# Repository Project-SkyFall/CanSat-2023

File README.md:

# Disclaimer
This README isn't finished and will be edited in near future

# CanSat-2023
This is a repository of the Czech CanSat team Project SkyFall, winner of CanSat's 2023 Czech national round

<div align="center">
  
</div>

## Documentation

<!-- About team -->

## About the team

  ### Vít Brázda
  <table><tr>
    <td width="250"></td>
    <td>Vít is responsible for data visualization running on ground station, as well as making index of habitability of planet, where CanSat is landing. He has a lot of experience regarding Python.</td>
  </tr></table>

  ### David Haisman
  <table><tr>
    <td width="250"></td>
    <td>David handles electronics and programming on our CanSat. He designed PCB's, made some libraries and wrote the whole CanSat code. During the development of the CanSat he gained a lot of experience regarding PCB design and programming in C++.</td>
  </tr></table>

  ### Radim Leština
  <table><tr>
    <td width="250"></td>
    <td>Radim is in charge of designing the outer construction of the CanSat itself. He has a lot of experience in designing and 3D printing mechanical contraptions.</td>
  </tr></table>

  ### Václav Horáček
  <table><tr>
    <td width="250"></td>
    <td>Václav is in charge of multiple departments, mainly the ones for documentation and recovery. In documentation he made the styles, graphics and oversees the documentation making process. His contribution in the recovery department is designing and sewing the CanSat's parachute.</td>
  </tr></table>

  ### Lukáš Nastoupil
  <table><tr>
    <td width="250"></td>
    <td>Lukáš designed and made the ground station, which is an essential part for our secondary mission. He designed the PCB's, modeled and programmed the ground station. He also worked on the real-time transmission of video from CanSat down to the ground station.</td>
  </tr></table>

  ### Adam Keřka
  <table><tr>
    <td width="250"></td>
    <td>Adam leads the team itself and also the department of publicity. This mainly includes maintaining social networks accounts and communicating with sponsors. He also designed a lot of the graphics used in advertising and posts on social networks.</td>
  </tr></table>

  ### Vladimír Kašpar
  Ing. Vladimír Kašpar is our mentor in the CanSat competition. We chose Vladimír Kašpar as our mentor based on his experience. In the CanSat 2019 he was a mentor of team Charles the fourth that made it to the European finale. He is also an electronics teacher at SPŠE a VOŠ Pardubice.

  ### Jan Novotný
  Jan Novotný is a freelance developer who makes web and mobile applications. He programmed the Project SkyFall webpage and supports our team on various other competitions and outgoings.

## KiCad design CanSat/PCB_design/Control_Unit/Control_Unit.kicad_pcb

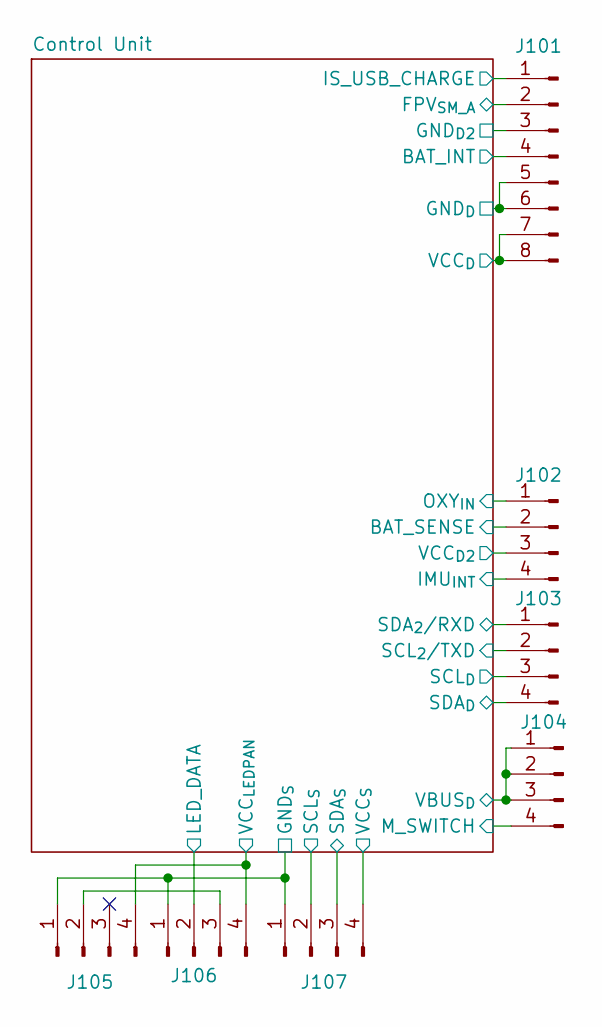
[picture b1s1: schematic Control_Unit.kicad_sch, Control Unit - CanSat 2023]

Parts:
J101: Conn_02x04_Male; PinHeader_2x04_P2.54mm_Vertical
J102, J103, J104: Conn_02x02_Male; PinHeader_2x02_P2.54mm_Vertical
J105, J106, J107: 009155004541006

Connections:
/Control Unit/BATT_INT: J101.4; also elsewhere on the board
/Control Unit/BAT_SENSE: J102.2; also elsewhere on the board
/Control Unit/FPV_{SM_A}: J101.2; also elsewhere on the board
/Control Unit/GND: J101.3, J101.5, J101.6, J105.1, J106.1, J107.1; also elsewhere on the board
/Control Unit/IMU_{INT}: J102.4; also elsewhere on the board
/Control Unit/IS_USB_CHARGE: J101.1; also elsewhere on the board
/Control Unit/LED_DATA: J106.2; also elsewhere on the board
/Control Unit/M_SWITCH: J104.4; also elsewhere on the board
/Control Unit/OXY_{IN}: J102.1; also elsewhere on the board
/Control Unit/SCL: J103.3, J107.2; also elsewhere on the board
/Control Unit/SCL_{2}/TXD: J103.2; also elsewhere on the board
/Control Unit/SDA: J103.4, J107.3; also elsewhere on the board
/Control Unit/SDA_{2}/RXD: J103.1; also elsewhere on the board
/Control Unit/VBUS: J104.1, J104.2, J104.3; also elsewhere on the board
/Control Unit/VCC: J101.7, J101.8, J102.3, J107.4; also elsewhere on the board
/Control Unit/VCC_{LEDPAN}: J105.4, J106.4; also elsewhere on the board
unnamed: J105.2, J106.3

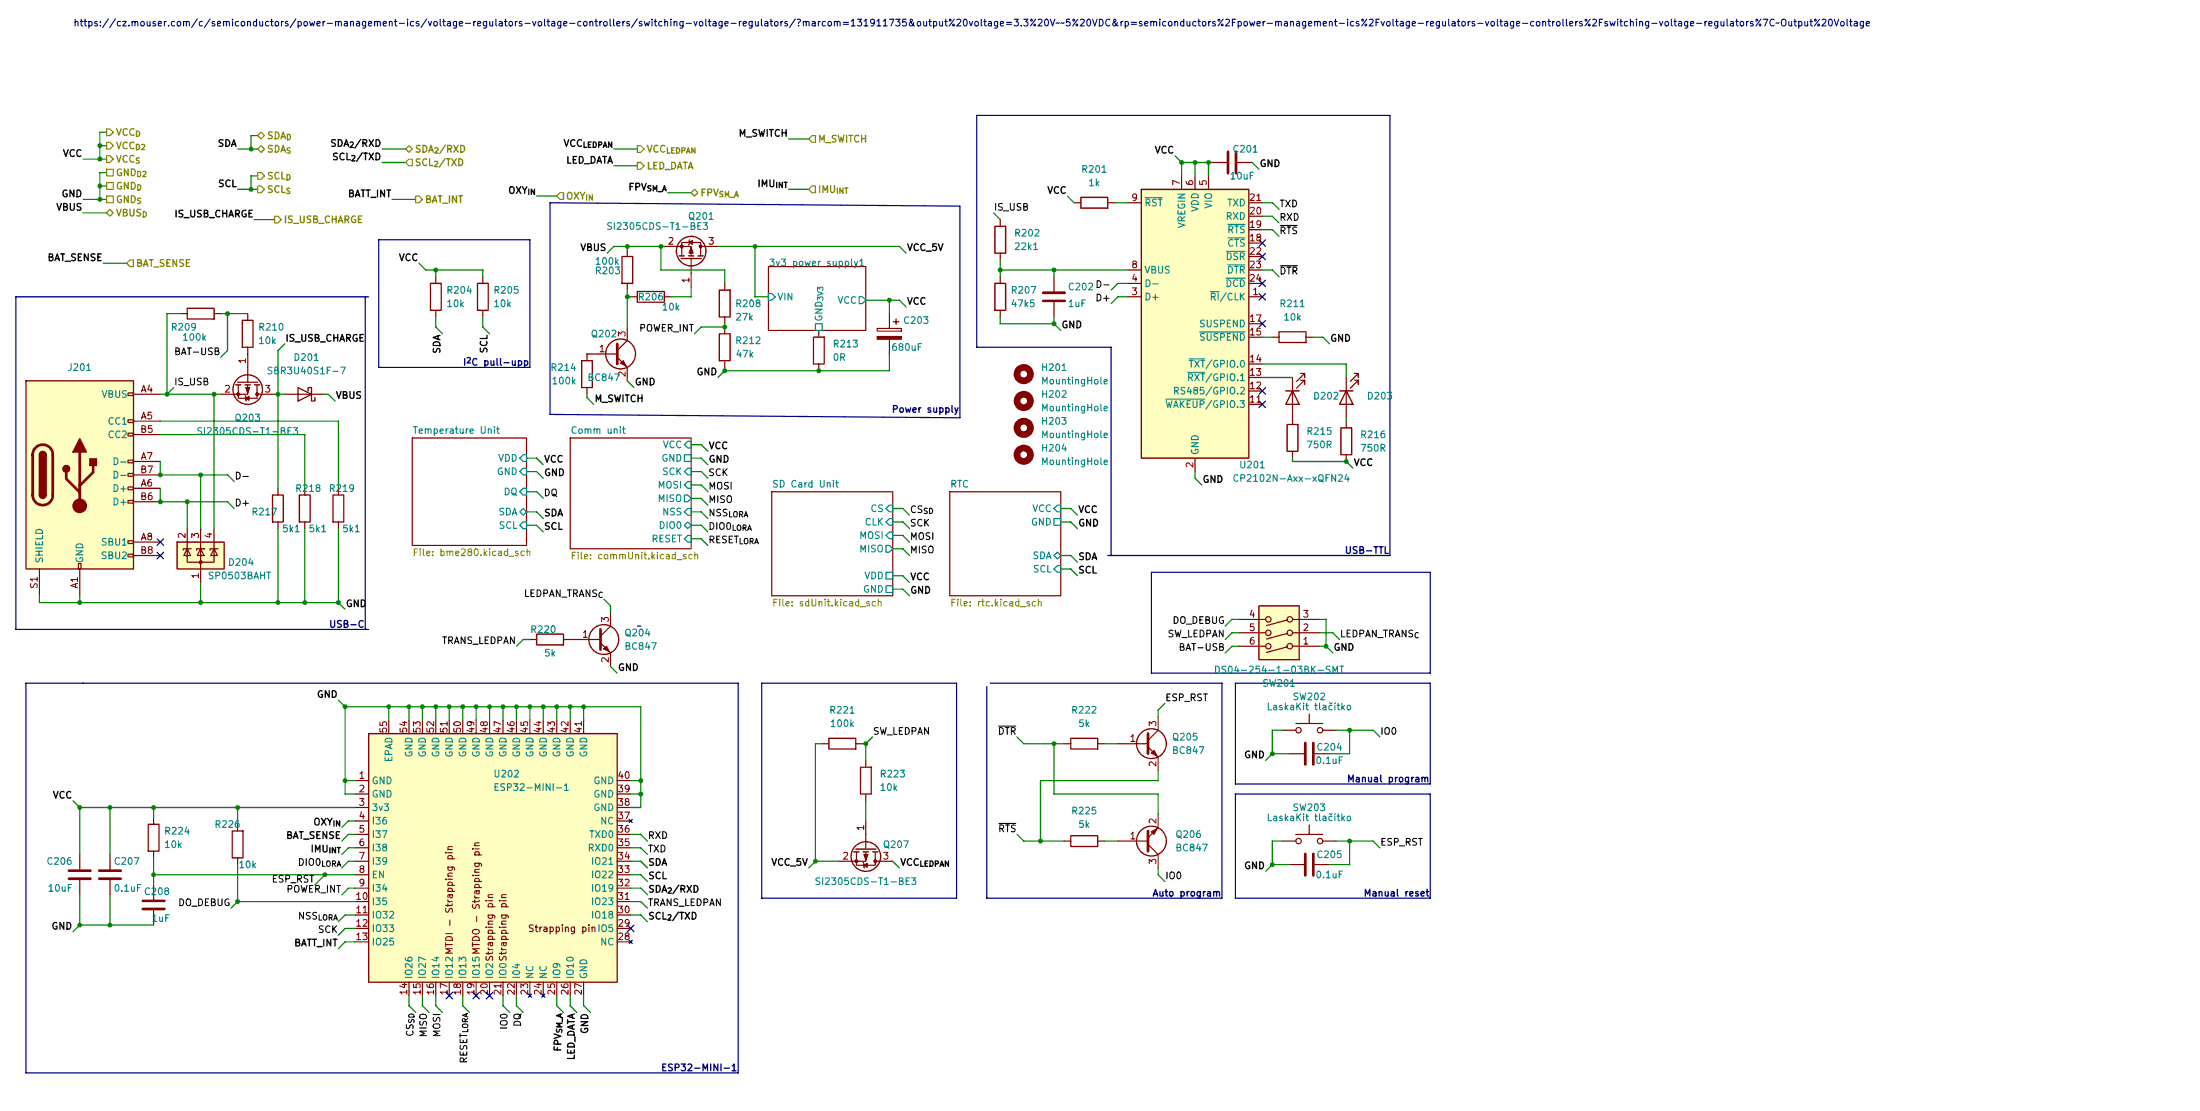
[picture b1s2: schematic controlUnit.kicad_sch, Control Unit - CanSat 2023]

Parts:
C201, C206: 10uF; C_0805_2012Metric
C202, C208: 1uF; C_0805_2012Metric
C203: 680uF; CP_Elec_6.3x7.7
C204, C205, C207: 0.1uF; C_0805_2012Metric
D201: SBR3U40S1F-7; D_SOD-123F
D202, D203: APT2012LSECK/J4-PRV; LED_0805_2012Metric
D204: SP0503BAHT; SOT-143
H201, H202, H203, H204: MountingHole; MountingHole_3.2mm_M3
J201: USB4110-GF-A; USB4110GFA
Q201, Q203, Q207: SI2305CDS-T1-BE3; SOT-23
Q202, Q204, Q205, Q206: BC847; SOT-23
R201: 1k; R_0805_2012Metric
R202: 22k1; R_0805_2012Metric
R203, R209, R214, R221: 100k; R_0805_2012Metric
R204, R205, R206, R210, R211, R223, R224, R226: 10k; R_0805_2012Metric
R207: 47k5; R_0805_2012Metric
R208: 27k; R_0805_2012Metric
R212: 47k; R_0805_2012Metric
R213: 0R; R_1206_3216Metric
R215, R216: 750R; R_0805_2012Metric
R217, R218, R219: 5k1; R_0805_2012Metric
R220, R222, R225: 5k; R_0805_2012Metric
SW201: DS04-254-1-03BK-SMT; SW_DIP_SPSTx03_Slide_Omron_A6S-310x_W8.9mm_P2.54mm
SW202, SW203: LaskaKit tlačítko; Tlačítko SMD LaskaKit
U201: CP2102N-Axx-xQFN24; QFN-24-1EP_4x4mm_P0.5mm_EP2.6x2.6mm
U202: ESP32-MINI-1

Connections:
/Control Unit/3v3 power supply1/GND_{3V3}: R213.2; also elsewhere on the board
/Control Unit/BAT-USB: R209.2, R210.1, SW201.6
/Control Unit/BATT_INT: U202.13 (IO25); also elsewhere on the board
/Control Unit/BAT_SENSE: U202.5 (I37); also elsewhere on the board
/Control Unit/CS_{SD}: U202.14 (IO26); also elsewhere on the board
/Control Unit/D+: D204.2 (K), J201.A6 (D+), J201.B6 (D+), U201.3 (D+)
/Control Unit/D-: D204.3 (K), J201.A7 (D-), J201.B7 (D-), U201.4 (D-)
/Control Unit/DIO0_{LORA}: U202.7 (I39); also elsewhere on the board
/Control Unit/DO_DEBUG: R226.1, SW201.4, U202.10 (I35)
/Control Unit/DQ: U202.22 (I04); also elsewhere on the board
/Control Unit/ESP_RST: C205.2, C208.1, Q205.3 (C), R224.2, SW203.2, U202.8 (EN)
/Control Unit/FPV_{SM_A}: U202.25 (IO9); also elsewhere on the board
/Control Unit/GND: C201.2, C202.2, C203.2, C204.1, C205.1, C206.2, C207.2, C208.2, D204.1 (A), J201.A1 (GND), J201.A12 (GND), J201.B1 (GND), J201.B12 (GND), J201.S1 (SHIELD), Q202.2 (E), Q204.2 (E), R207.2, R211.2, R212.2, R213.1, R217.2, R218.2, R219.2, SW201.1, SW201.3, SW202.1, SW203.1, U201.2 (GND), U201.25 (GND), U202.1 (GND), U202.2 (GND), U202.27 (GND), U202.38 (GND), U202.39 (GND), U202.40 (GND), U202.41 (GND), U202.42 (GND), U202.43 (GND), U202.44 (GND), U202.45 (GND), U202.46 (GND), U202.47 (GND), U202.48 (GND), U202.49 (GND), U202.50 (GND), U202.51 (GND), U202.52 (GND), U202.53 (GND), U202.54 (GND), U202.55 (EPAD); also elsewhere on the board
/Control Unit/IMU_{INT}: U202.6 (I38); also elsewhere on the board
/Control Unit/IO0: C204.2, Q206.3 (C), SW202.2, U202.21 (IO0)
/Control Unit/IS_USB: D204.4 (K), J201.A4 (VBUS), J201.A9 (VBUS), J201.B4 (VBUS), J201.B9 (VBUS), Q203.2 (S), R202.2, R209.1
/Control Unit/IS_USB_CHARGE: D201.2 (A), Q203.3 (D), R217.1; also elsewhere on the board
/Control Unit/LEDPAN_TRANS_{C}: Q204.3 (C), SW201.2
/Control Unit/LED_DATA: U202.26 (IO10); also elsewhere on the board
/Control Unit/MISO: U202.15 (IO27); also elsewhere on the board
/Control Unit/MOSI: U202.16 (IO14); also elsewhere on the board
/Control Unit/M_SWITCH: R214.1; also elsewhere on the board
/Control Unit/NSS_{LORA}: U202.11 (IO32); also elsewhere on the board
/Control Unit/OXY_{IN}: U202.4 (I36); also elsewhere on the board
/Control Unit/POWER_INT: R208.1, R212.1, U202.9 (I34)
/Control Unit/RESET_{LORA}: U202.18 (IO13); also elsewhere on the board
/Control Unit/RXD: U201.20 (RXD), U202.36 (TXD0)
/Control Unit/SCK: U202.12 (IO33); also elsewhere on the board
/Control Unit/SCL: R205.2, U202.33 (IO22); also elsewhere on the board
/Control Unit/SCL_{2}/TXD: U202.30 (IO18); also elsewhere on the board
/Control Unit/SDA: R204.2, U202.34 (IO21); also elsewhere on the board
/Control Unit/SDA_{2}/RXD: U202.32 (IO19); also elsewhere on the board
/Control Unit/SW_LEDPAN: R221.2, R223.2, SW201.5
/Control Unit/TRANS_LEDPAN: R220.1, U202.31 (IO23)
/Control Unit/TXD: U201.21 (TXD), U202.35 (RXD0)
/Control Unit/VBUS: D201.1 (K), Q201.2 (S), R203.1, R208.2; also elsewhere on the board
/Control Unit/VCC: C201.1, C203.1, C206.1, C207.1, R201.1, R204.1, R205.1, R215.1, R216.1, R224.1, R226.2, U201.5 (VIO), U201.6 (VDD), U201.7 (VREGIN), U202.3 (3v3); also elsewhere on the board
/Control Unit/VCC_5V: Q201.3 (D), Q207.2 (S), R221.1; also elsewhere on the board
/Control Unit/VCC_{LEDPAN}: Q207.3 (D); also elsewhere on the board
/Control Unit/~DTR: Q206.2 (E), R222.1, U201.23 (~DTR)
/Control Unit/~RTS: Q205.2 (E), R225.1, U201.19 (~RTS)
unnamed: C202.1, R202.1, R207.1, U201.8 (VBUS)
unnamed: D202.1 (K), U201.13 (~RXT/GPIO.1)
unnamed: D202.2 (A), R215.2
unnamed: D203.1 (K), U201.14 (~TXT/GPIO.0)
unnamed: D203.2 (A), R216.2
unnamed: J201.A5 (CC1), R219.1
unnamed: J201.B5 (CC2), R218.1
unnamed: Q201.1 (G), R206.1
unnamed: Q202.1 (B), R214.2
unnamed: Q202.3 (C), R203.2, R206.2
unnamed: Q203.1 (G), R210.2
unnamed: Q204.1 (B), R220.2
unnamed: Q205.1 (B), R222.2
unnamed: Q206.1 (B), R225.2
unnamed: Q207.1 (G), R223.1
unnamed: R201.2, U201.9 (~RST)
unnamed: R211.1, U201.15 (~SUSPEND)

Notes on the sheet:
USB-TTL
I^{2}C pull-upp
Auto program
ESP32-MINI-1
USB-C
Power supply
Manual reset
https://cz.mouser.com/c/semiconductors/power-management-ics/voltage-regulators-voltage-controllers/switching-voltage-regulators/?marcom=131911735&output%20voltage=3.3%20V~~5%20VDC&rp=semiconductors%2Fpower-management-ics%2Fvoltage-regulators-voltage-controllers%2Fswitching-voltage-regulators%7C~Out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
Manual program

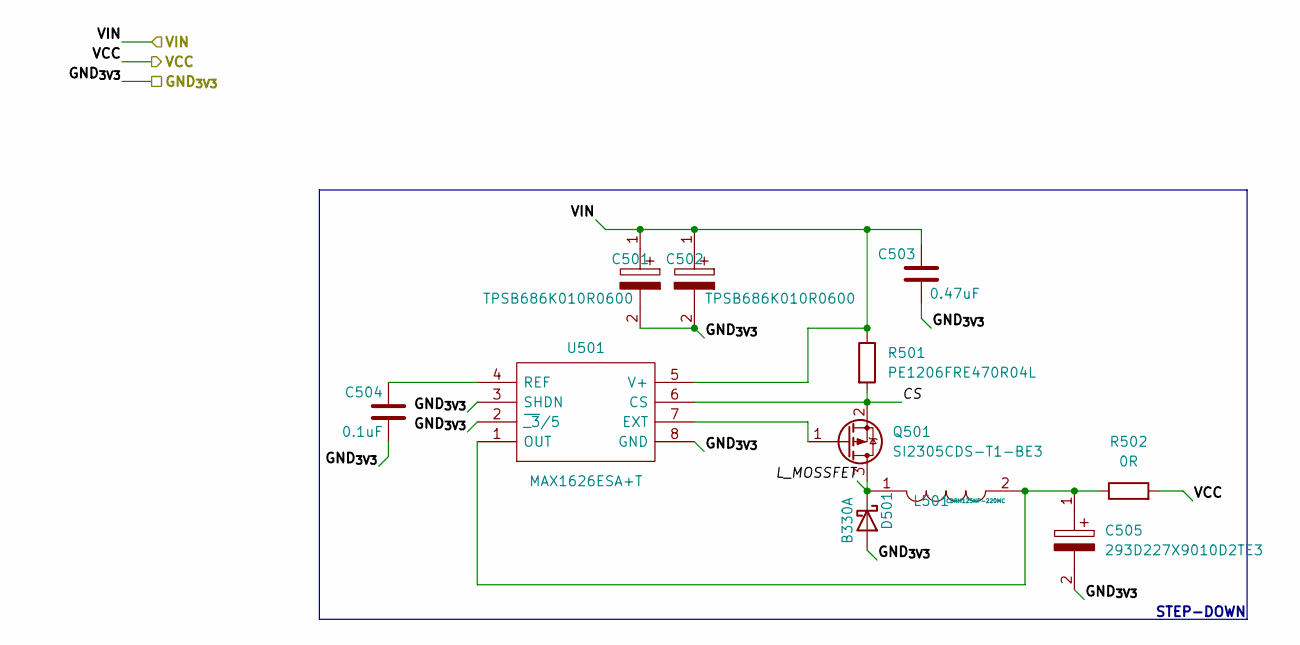
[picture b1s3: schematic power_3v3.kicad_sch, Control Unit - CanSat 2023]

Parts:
C501, C502: TPSB686K010R0600; CP_EIA-3528-21_Kemet-B; Mouser Part Number 581-TPSB686K010R0600
C503: 0.47uF; C_0805_2012Metric
C504: 0.1uF; C_0805_2012Metric
C505: 293D227X9010D2TE3; CP_EIA-7343-31_Kemet-D; Mouser Part Number 74-293D227X9010D2TE3
D501: B330A; D_SMA
L501: CDRH125NP-220MC; CDRH125101MC; Mouser Part Number 851-CDRH125NP-220MC
Q501: SI2305CDS-T1-BE3; SOT-23
R501: PE1206FRE470R04L; R_1206_Current
R502: 0R; R_1206_3216Metric
U501: MAX1626ESA+T; SOIC127P600X175-8N; Mouser Part Number 700-MAX1626ESAT

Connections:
/Control Unit/3v3 power supply1/CS: Q501.2 (S), R501.2, U501.6 (CS)
/Control Unit/3v3 power supply1/GND_{3V3}: C501.2, C502.2, C503.2, C504.2, C505.2, D501.2 (A), U501.2 (~_3/5), U501.3 (SHDN), U501.8 (GND); also elsewhere on the board
/Control Unit/3v3 power supply1/L_MOSSFET: D501.1 (K), L501.1, Q501.3 (D)
/Control Unit/VCC: R502.2; also elsewhere on the board
/Control Unit/VCC_5V: C501.1, C502.1, C503.1, R501.1, U501.5 (V+); also elsewhere on the board
unnamed: C504.1, U501.4 (REF)
unnamed: C505.1, L501.2, R502.1, U501.1 (OUT)
unnamed: Q501.1 (G), U501.7 (EXT)

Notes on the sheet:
STEP-DOWN

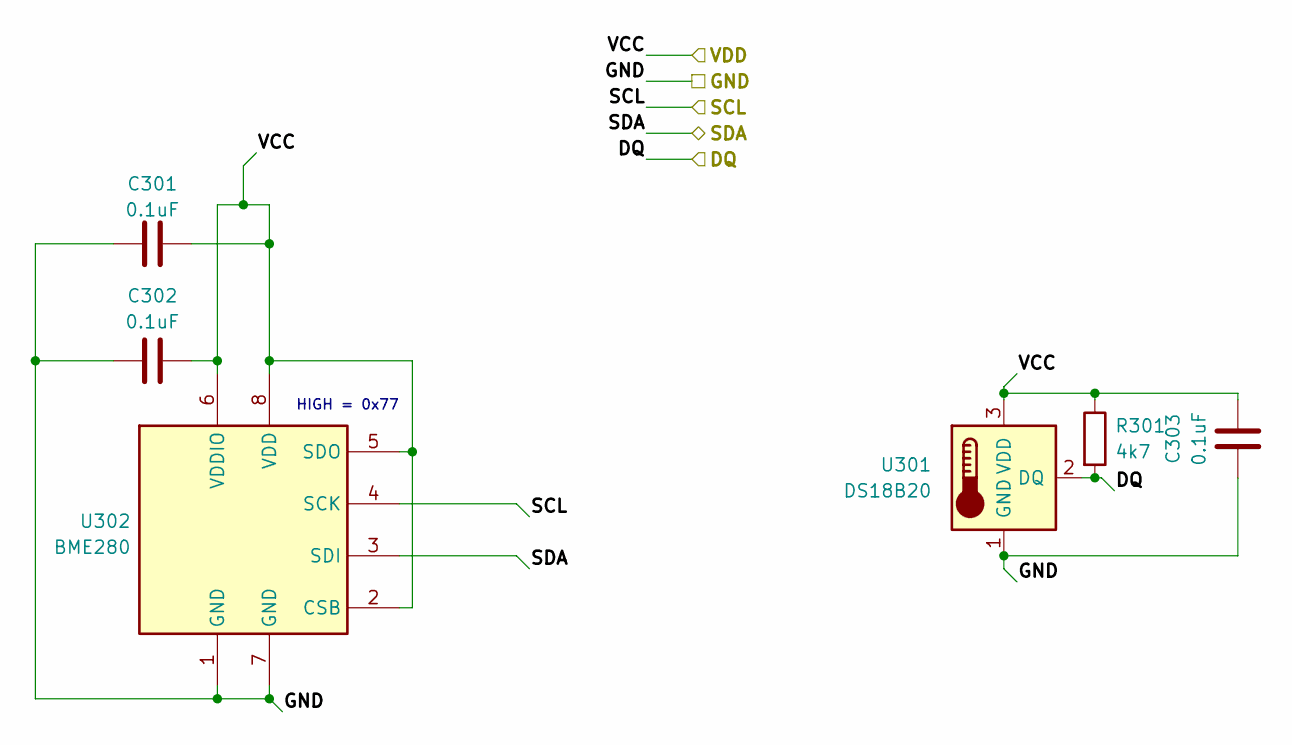
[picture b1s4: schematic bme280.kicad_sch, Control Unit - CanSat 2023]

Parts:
C301, C302, C303: 0.1uF; C_0805_2012Metric
R301: 4k7; R_0805_2012Metric
U301: DS18B20; TO-92_Inline
U302: BME280; Bosch_LGA-8_2.5x2.5mm_P0.65mm_ClockwisePinNumbering

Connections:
/Control Unit/DQ: R301.2, U301.2 (DQ); also elsewhere on the board
/Control Unit/GND: C301.2, C302.2, C303.2, U301.1 (GND), U302.1 (GND), U302.7 (GND); also elsewhere on the board
/Control Unit/SCL: U302.4 (SCK); also elsewhere on the board
/Control Unit/SDA: U302.3 (SDI); also elsewhere on the board
/Control Unit/VCC: C301.1, C302.1, C303.1, R301.1, U301.3 (VDD), U302.2 (CSB), U302.5 (SDO), U302.6 (VDDIO), U302.8 (VDD); also elsewhere on the board

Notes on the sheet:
HIGH = 0x77

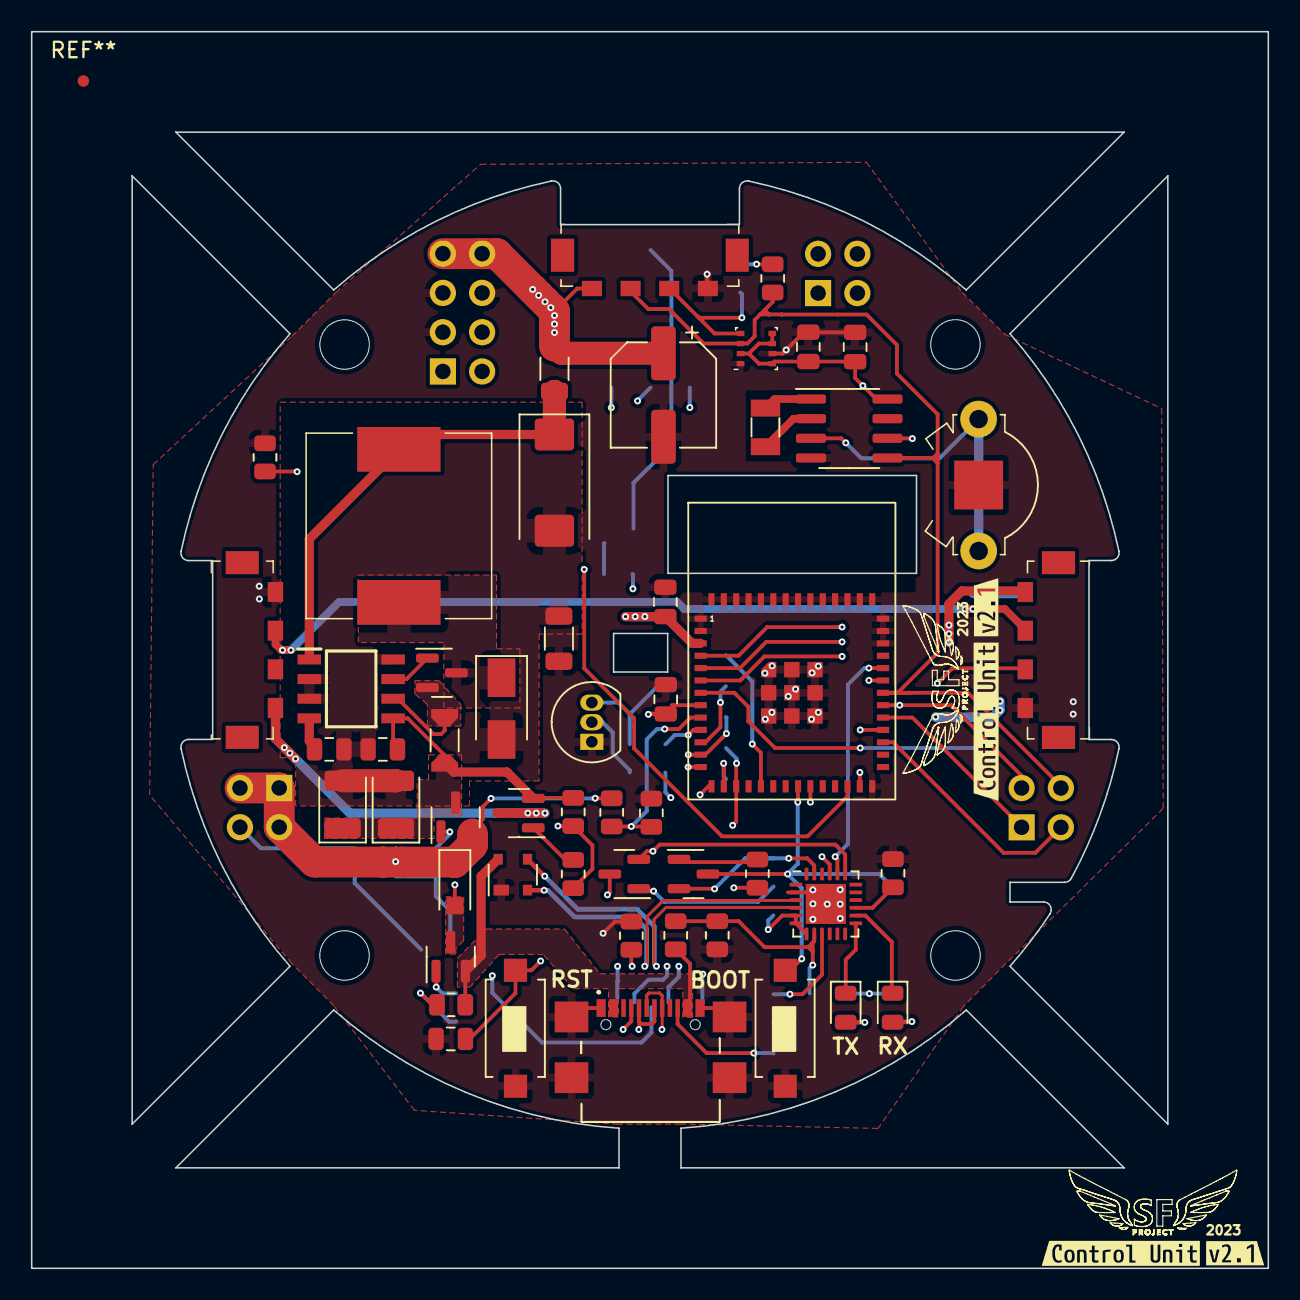
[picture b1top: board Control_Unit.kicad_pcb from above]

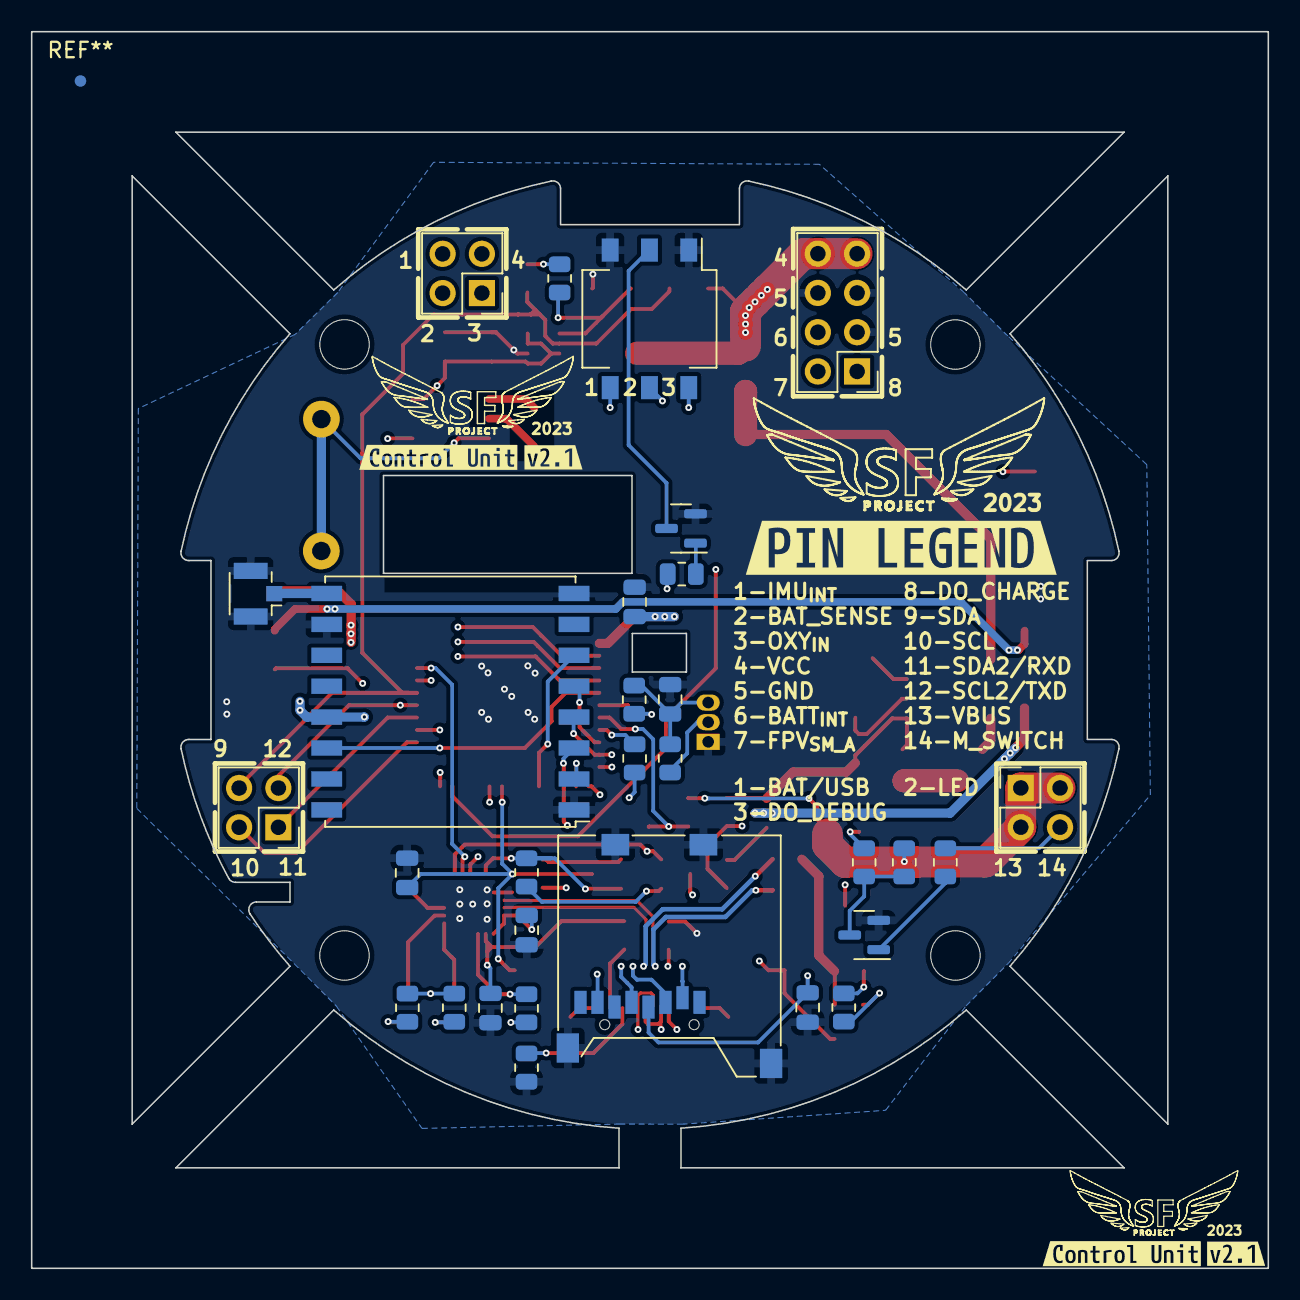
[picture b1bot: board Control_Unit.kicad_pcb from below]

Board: 4 copper layers, 80.0 x 80.0 mm, 95 parts (35 on the bottom side), 68 nets.

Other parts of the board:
AE401: Antenna_Shield; U.FL_Hirose_U.FL-R-SMT-1_Vertical
BT701: Backup battery; 2989
C601: 0.1uF; C_0805_2012Metric
J601: Micro_SD_Card 823-046; DS1139-05
U401: RFM96W-433S2; HOPERF_RFM9XW_SMD
U701: PT7C4339; SOIC-8-1EP_3.9x4.9mm_P1.27mm_EP2.29x3mm
Y701: ECS-.327-6-34B-C-TR; ECX-31B
kibuzzard-63BEB0CF, kibuzzard-63BEB0CF#2, kibuzzard-63BEB0CF#3, kibuzzard-63BEB0CF#4: G***; kibuzzard-63BEB0CF
kibuzzard-63BEB9E1: G***; kibuzzard-63BEB9E1
kibuzzard-644421C3: G***; kibuzzard-644421C3
kibuzzard-644421CD: G***; kibuzzard-644421CD
kibuzzard-644421E6: G***; kibuzzard-644421E6
kibuzzard-644422F5: G***; kibuzzard-644422F5

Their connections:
/Control Unit/CS_{SD}: J601.2 (DAT3/CD); also elsewhere on the board
/Control Unit/DIO0_{LORA}: U401.14 (DIO0); also elsewhere on the board
/Control Unit/GND: AE401.2 (Shield), BT701.2 (-), C601.1, J601.6 (VSS), J601.9 (SHIELD), U401.1 (GND), U401.8 (GND), U401.10 (GND), U701.4 (GND); also elsewhere on the board
/Control Unit/MISO: J601.7 (DAT0), U401.2 (MISO); also elsewhere on the board
/Control Unit/MOSI: J601.3 (CMD), U401.3 (MOSI); also elsewhere on the board
/Control Unit/NSS_{LORA}: U401.5 (NSS); also elsewhere on the board
/Control Unit/RESET_{LORA}: U401.6 (RESET); also elsewhere on the board
/Control Unit/SCK: J601.5 (CLK), U401.4 (SCK); also elsewhere on the board
/Control Unit/SCL: U701.6 (SCL); also elsewhere on the board
/Control Unit/SDA: U701.5 (SDA); also elsewhere on the board
/Control Unit/VCC: C601.2, J601.4 (VDD), U401.13 (3.3V), U701.8 (V_{CC}); also elsewhere on the board
unnamed: AE401.1 (A), U401.9 (ANT)
unnamed: BT701.1 (+), U701.3 (V_{BACKUP})
unnamed: U701.1 (X1), Y701.2
unnamed: U701.2 (X2), Y701.1

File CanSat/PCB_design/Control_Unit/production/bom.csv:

Designator,Footprint,Quantity,Value,LCSC Part #
AE401,U.FL_Hirose_U.FL-R-SMT-1_Vertical,1,Antenna_Shield,
BT701,2989,1,Backup battery,
"C201, C206",C_0805_2012Metric,2,10uF,
"C202, C208",C_0805_2012Metric,2,1uF,
C203,CP_Elec_6.3x7.7,1,680uF,
"C204, C205, C207, C301, C302, C303, C504, C601",C_0805_2012Metric,8,0.1uF,
"C501, C502",CP_EIA-3528-21_Kemet-B,2,TPSB686K010R0600,
C503,C_0805_2012Metric,1,0.47uF,
C505,CP_EIA-7343-31_Kemet-D,1,293D227X9010D2TE3,
D201,D_SOD-123F,1,SBR3U40S1F-7,
"D202, D203",LED_0805_2012Metric,2,APT2012LSECK/J4-PRV,
D204,SOT-143,1,SP0503BAHT,
D501,D_SMA,1,B330A,
J101,PinHeader_2x04_P2.54mm_Vertical,1,Conn_02x04_Male,
"J102, J103, J104",PinHeader_2x02_P2.54mm_Vertical,3,Conn_02x02_Male,
"J105, J106, J107",009155004541006,3,009155004541006,
J201,USB4110GFA,1,USB4110-GF-A,
J601,DS1139-05,1,Micro_SD_Card 823-046,
L501,CDRH125101MC,1,CDRH125NP-220MC,
"Q201, Q203, Q207, Q501",SOT-23,4,SI2305CDS-T1-BE3,
"Q202, Q204, Q205, Q206",SOT-23,4,BC847,
R201,R_0805_2012Metric,1,1k,
R202,R_0805_2012Metric,1,22k1,
"R203, R209, R214, R221",R_0805_2012Metric,4,100k,
"R204, R205, R206, R210, R211, R223, R224, R226",R_0805_2012Metric,8,10k,
R207,R_0805_2012Metric,1,47k5,
R208,R_0805_2012Metric,1,27k,
R212,R_0805_2012Metric,1,47k,
"R213, R502",R_1206_3216Metric,2,0R,
"R215, R216",R_0805_2012Metric,2,750R,
"R217, R218, R219",R_0805_2012Metric,3,5k1,
"R220, R222, R225",R_0805_2012Metric,3,5k,
R301,R_0805_2012Metric,1,4k7,
R501,R_1206_Current,1,PE1206FRE470R04L,
SW201,SW_DIP_SPSTx03_Slide_Omron_A6S-310x_W8.9mm_P2.54mm,1,DS04-254-1-03BK-SMT,
"SW202, SW203",Tlačítko SMD LaskaKit,2,LaskaKit tlačítko,
U201,QFN-24-1EP_4x4mm_P0.5mm_EP2.6x2.6mm,1,CP2102N-Axx-xQFN24,
U202,ESP32-MINI-1,1,ESP32-MINI-1,
U301,TO-92_Inline,1,DS18B20,
U302,Bosch_LGA-8_2.5x2.5mm_P0.65mm_ClockwisePinNumbering,1,BME280,
U401,HOPERF_RFM9XW_SMD,1,RFM96W-433S2,
U501,SOIC127P600X175-8N,1,MAX1626ESA+T,
U701,SOIC-8-1EP_3.9x4.9mm_P1.27mm_EP2.29x3mm,1,PT7C4339,
Y701,ECX-31B,1,ECS-.327-6-34B-C-TR,

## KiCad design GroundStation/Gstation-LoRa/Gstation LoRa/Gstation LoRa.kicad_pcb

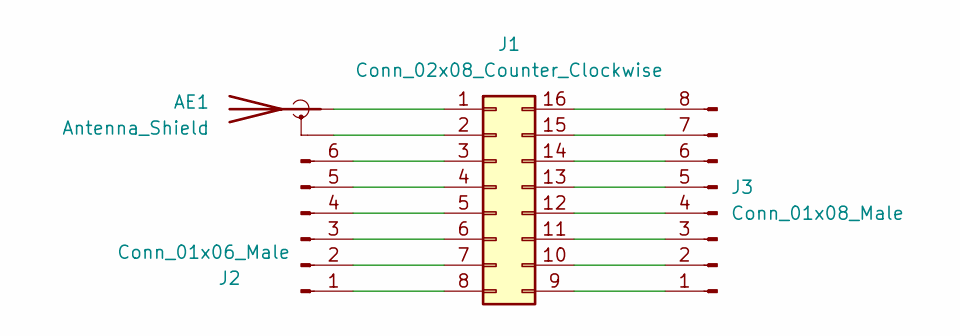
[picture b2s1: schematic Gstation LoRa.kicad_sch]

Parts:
AE1: Antenna_Shield; U.FL_Hirose_U.FL-R-SMT-1_Vertical
J1: Conn_02x08_Counter_Clockwise; HOPERF_RFM9XW_SMD
J2: Conn_01x06_Male; PinHeader_1x06_P2.54mm_Vertical
J3: Conn_01x08_Male; PinHeader_1x08_P2.54mm_Vertical

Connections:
unnamed: AE1.1 (A), J1.1
unnamed: AE1.2 (Shield), J1.2
unnamed: J1.3, J2.6
unnamed: J1.4, J2.5
unnamed: J1.5, J2.4
unnamed: J1.6, J2.3
unnamed: J1.7, J2.2
unnamed: J1.8, J2.1
unnamed: J1.9, J3.1
unnamed: J1.10, J3.2
unnamed: J1.11, J3.3
unnamed: J1.12, J3.4
unnamed: J1.13, J3.5
unnamed: J1.14, J3.6
unnamed: J1.15, J3.7
unnamed: J1.16, J3.8

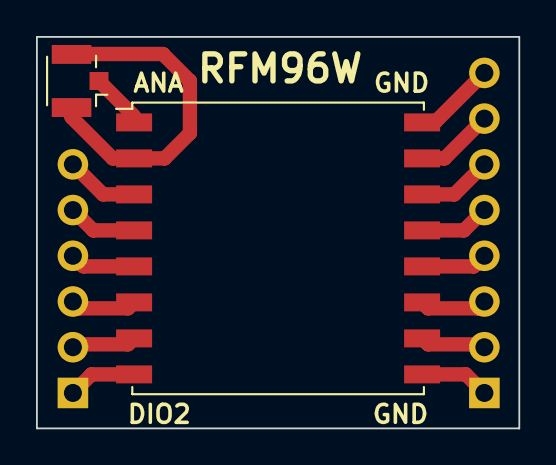
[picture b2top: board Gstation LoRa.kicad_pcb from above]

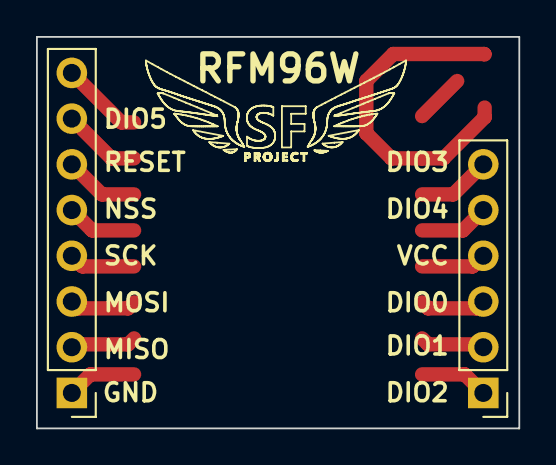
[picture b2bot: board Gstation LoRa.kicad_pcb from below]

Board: 2 copper layers, 26.8 x 21.8 mm, 4 parts (2 on the bottom side), 16 nets.

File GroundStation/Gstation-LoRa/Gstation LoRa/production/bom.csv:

Designator,Footprint,Quantity,Value,LCSC Part #
AE1,U.FL_Hirose_U.FL-R-SMT-1_Vertical,1,Antenna_Shield,
J1,HOPERF_RFM9XW_SMD,1,Conn_02x08_Counter_Clockwise,
J2,PinHeader_1x06_P2.54mm_Vertical,1,Conn_01x06_Male,
J3,PinHeader_1x08_P2.54mm_Vertical,1,Conn_01x08_Male,
